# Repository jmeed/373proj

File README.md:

373proj
=======

The Smart Watch Project

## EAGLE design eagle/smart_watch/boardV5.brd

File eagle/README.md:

Before you open the file in eagle make sure to go to library->use and add all the files in the lbr directory

Major Links for Documentation

ARM M-0
* LCP 1114 48 pin : http://www.nxp.com/documents/data_sheet/LPC111X.pdf

Power System:
* MAX17043G+U (Fuel Gage): http://dlnmh9ip6v2uc.cloudfront.net/datasheets/Prototyping/MAX17043-MAX17044.pdf 
 * I2C
* MCP73831T (Battery Charger): http://www.sparkfun.com/datasheets/Prototyping/Batteries/MCP73831T.pdf
* TPS61200 (Boost Converter): http://www.sparkfun.com/datasheets/Prototyping/tps61200.pdf
* MIC5205 (LDO) : http://www.micrel.com/_PDF/mic5205.pdf

Screen: 
* uOLED-G2 : http://www.4dsystems.com.au/downloads/microOLED/uOLED-128-G2/Docs/uOLED-128-G2-Datasheet-REV1.pdf
			 Serial Communication documentation: http://www.4dsystems.com.au/downloads/Software/4D-Workshop4-IDE/Docs/Serial/GOLDELOX-SPE-COMMAND-SET-REV1.3.pdf
  * UART

Bluetooth:
* SPI/UART
  
Perf:
* ADXL345 (Accelerometer): http://www.sparkfun.com/datasheets/Sensors/Accelerometer/ADXL345.pdf
  * SPI/I2C
* Vibrator (2 pins) 
  * 1 pin gpio. Other pin gnd
* Joystick : http://www.sparkfun.com/datasheets/Components/Buttons/SF303GJ26-3.pdf
  *  NOTE: I am not sure how to get this on the board as it is big and the board will be covered on both sides.
  *  5 pins GPIO. 1 pin power

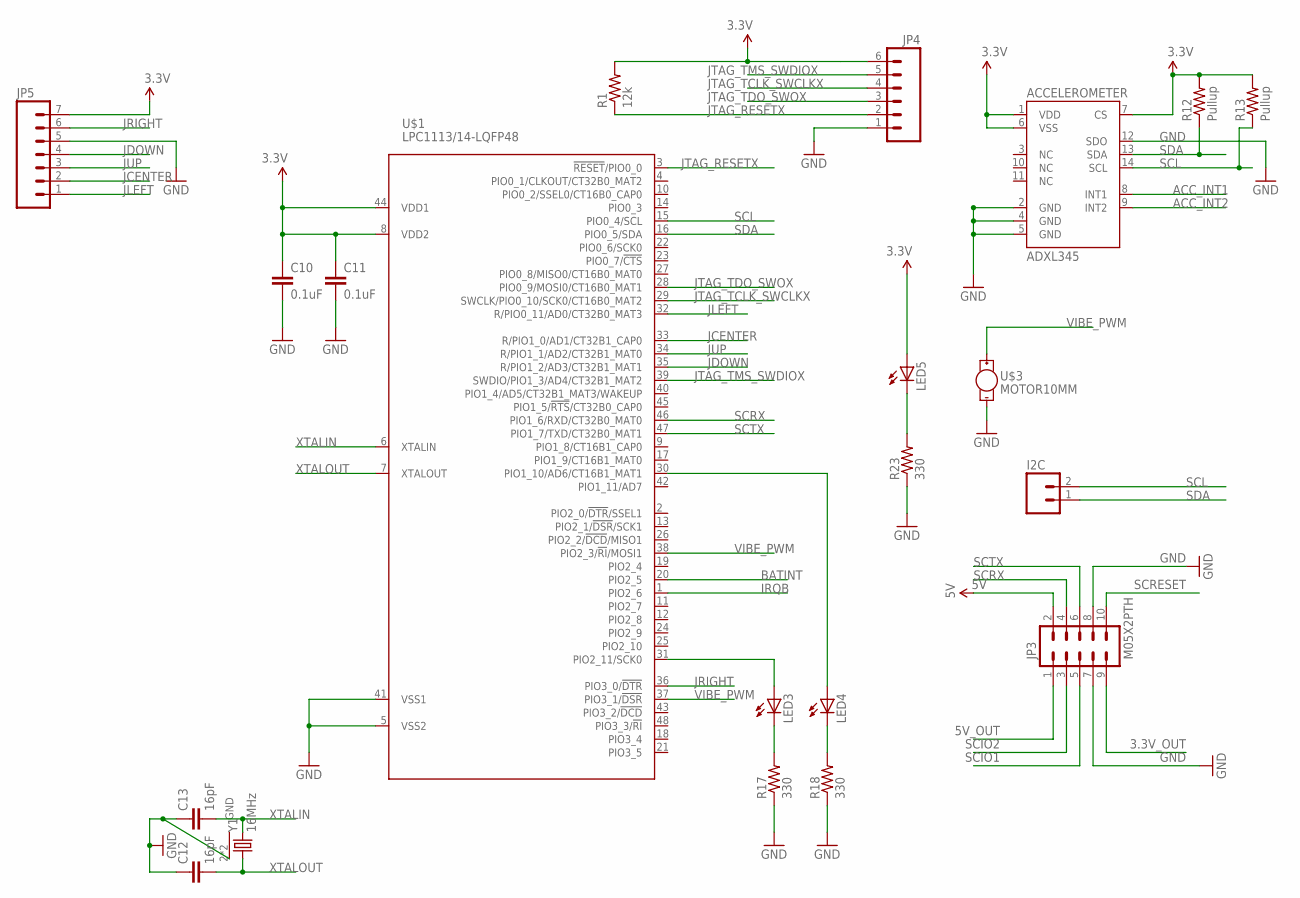
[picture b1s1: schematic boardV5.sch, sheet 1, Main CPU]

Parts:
ACCELEROMETER: ADXL345; LGA14
C10, C11: 0.1uF; 0603-CAP
C12, C13: 16pF; 0603-CAP
I2C: M02POLAR; MOLEX-1X2
JP3: M05X2PTH; AVR_ICSP
JP4: M06POLAR; MOLEX-1X6
JP5: M07; 1X07
LED3, LED4, LED5: LED0603; LED-0603
R1: 12k; 0603-RES
R12, R13: Pullup; 0603-RES
R17, R18, R23: 330; 0603-RES
U$1: LPC1113/14-LQFP48; LQFP48
U$3: MOTOR10MM; VIBE-MOTOR-10MM
Y1: 16MHz; CRYSTAL-SMD-5X3

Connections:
3.3V: ACCELEROMETER.1 (VDD), ACCELEROMETER.6 (VSS), ACCELEROMETER.7 (CS), C10.1, C11.1, JP4.6, JP5.7, LED5.A, R1.2, R12.2, R13.2, U$1.8 (VDD2), U$1.44 (VDD1); also elsewhere on the board
3.3V_OUT: JP3.9
5V: JP3.2; also elsewhere on the board
5V_OUT: JP3.1
ACC_INT1: ACCELEROMETER.8 (INT1)
ACC_INT2: ACCELEROMETER.9 (INT2)
BATINT: U$1.20 (PIO2_5); also elsewhere on the board
GND: ACCELEROMETER.2 (GND), ACCELEROMETER.4 (GND), ACCELEROMETER.5 (GND), ACCELEROMETER.12 (SDO), C10.2, C11.2, C12.1, C13.1, JP3.7, JP3.8, JP4.1, JP5.5, R17.1, R18.1, R23.1, U$1.5 (VSS2), U$1.41 (VSS1), U$3.-, Y1.2 (GND), Y1.4 (GND); also elsewhere on the board
IRQB: U$1.1 (PIO2_6); also elsewhere on the board
JCENTER: JP5.2, U$1.33 (R/PIO1_0/AD1/CT32B1_CAP0)
JDOWN: JP5.4, U$1.35 (R/PIO1_2/AD3/CT32B1_MAT1)
JLEFT: JP5.1, U$1.32 (R/PIO0_11/AD0/CT32B0_MAT3)
JRIGHT: JP5.6, U$1.36 (PIO3_0/!DTR!)
JTAG_RESETX: JP4.2, R1.1, U$1.3 (!RESET!/PIO0_0)
JTAG_TCLK_SWCLKX: JP4.4, U$1.29 (SWCLK/PIO0_10/SCK0/CT16B0_MAT2)
JTAG_TDO_SWOX: JP4.3, U$1.28 (PIO0_9/MOSI0/CT16B0_MAT1)
JTAG_TMS_SWDIOX: JP4.5, U$1.39 (SWDIO/PIO1_3/AD4/CT32B1_MAT2)
JUP: JP5.3, U$1.34 (R/PIO1_1/AD2/CT32B1_MAT0)
unnamed: LED3.A, U$1.31 (PIO2_11/SCK0)
unnamed: LED4.A, U$1.30 (PIO1_10/AD6/CT16B1_MAT1)
unnamed: LED3.C, R17.2
unnamed: LED4.C, R18.2
unnamed: LED5.C, R23.2
SCIO1: JP3.5
SCIO2: JP3.3
SCL: ACCELEROMETER.14 (SCL), I2C.2, R13.1, U$1.15 (PIO0_4/SCL); also elsewhere on the board
SCRESET: JP3.10
SCRX: JP3.4, U$1.46 (PIO1_6/RXD/CT32B0_MAT0)
SCTX: JP3.6, U$1.47 (PIO1_7/TXD/CT32B0_MAT1)
SDA: ACCELEROMETER.13 (SDA), I2C.1, R12.1, U$1.16 (PIO0_5/SDA); also elsewhere on the board
VIBE_PWM: U$1.37 (PIO3_1/!DSR!), U$1.38 (PIO2_3/!RI!/MOSI1), U$3.+
XTALIN: C13.2, U$1.6 (XTALIN), Y1.3 (2)
XTALOUT: C12.2, U$1.7 (XTALOUT), Y1.1

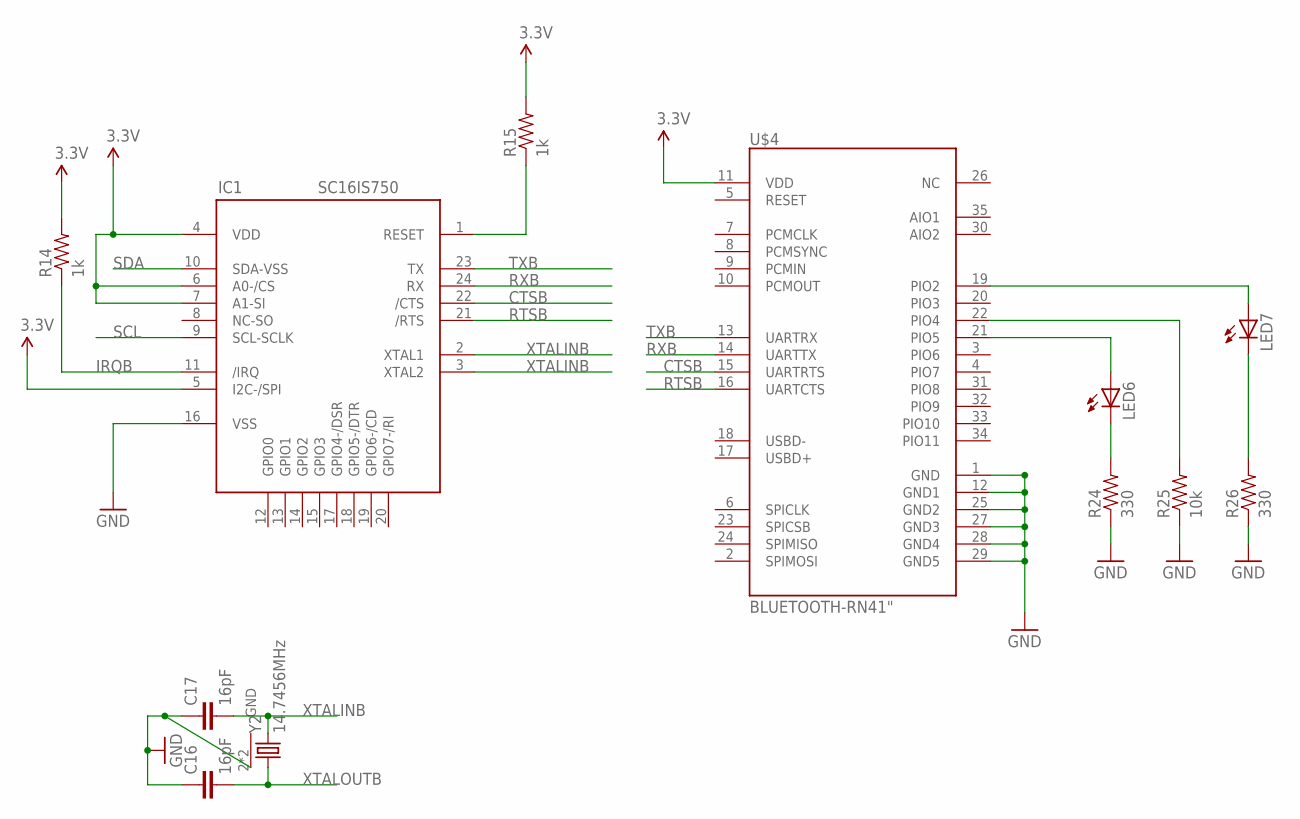
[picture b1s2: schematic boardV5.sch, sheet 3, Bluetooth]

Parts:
C16, C17: 16pF; 0603-CAP
IC1: SC16IS750; QFN-24
LED6, LED7: LED0603; LED-0603
R14, R15: 1k; 0603-RES
R24, R26: 330; 0603-RES
R25: 10k; 0603-RES
U$4: BLUETOOTH-RN41"; RN41
Y2: 14.7456MHz; CRYSTAL-SMD-5X3

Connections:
3.3V: IC1.4 (VDD), IC1.5 (I2C-/SPI), IC1.6 (A0-/CS), IC1.7 (A1-SI), R14.2, R15.2, U$4.11 (VDD); also elsewhere on the board
CTSB: IC1.22 (/CTS), U$4.15 (UARTRTS)
GND: C16.1, C17.1, IC1.16 (VSS), R24.1, R25.1, R26.1, U$4.1 (GND), U$4.12 (GND1), U$4.25 (GND2), U$4.27 (GND3), U$4.28 (GND4), U$4.29 (GND5), Y2.2 (GND), Y2.4 (GND); also elsewhere on the board
IRQB: IC1.11 (/IRQ), R14.1; also elsewhere on the board
unnamed: IC1.1 (RESET), R15.1
unnamed: LED7.A, U$4.19 (PIO2)
unnamed: R25.2, U$4.22 (PIO4)
unnamed: LED6.A, U$4.21 (PIO5)
unnamed: LED6.C, R24.2
unnamed: LED7.C, R26.2
RTSB: IC1.21 (/RTS), U$4.16 (UARTCTS)
RXB: IC1.24 (RX), U$4.14 (UARTTX)
SCL: IC1.9 (SCL-SCLK); also elsewhere on the board
SDA: IC1.10 (SDA-VSS); also elsewhere on the board
TXB: IC1.23 (TX), U$4.13 (UARTRX)
XTALINB: C17.2, IC1.2 (XTAL1), Y2.3 (2)
XTALOUTB: C16.2, IC1.3 (XTAL2), Y2.1

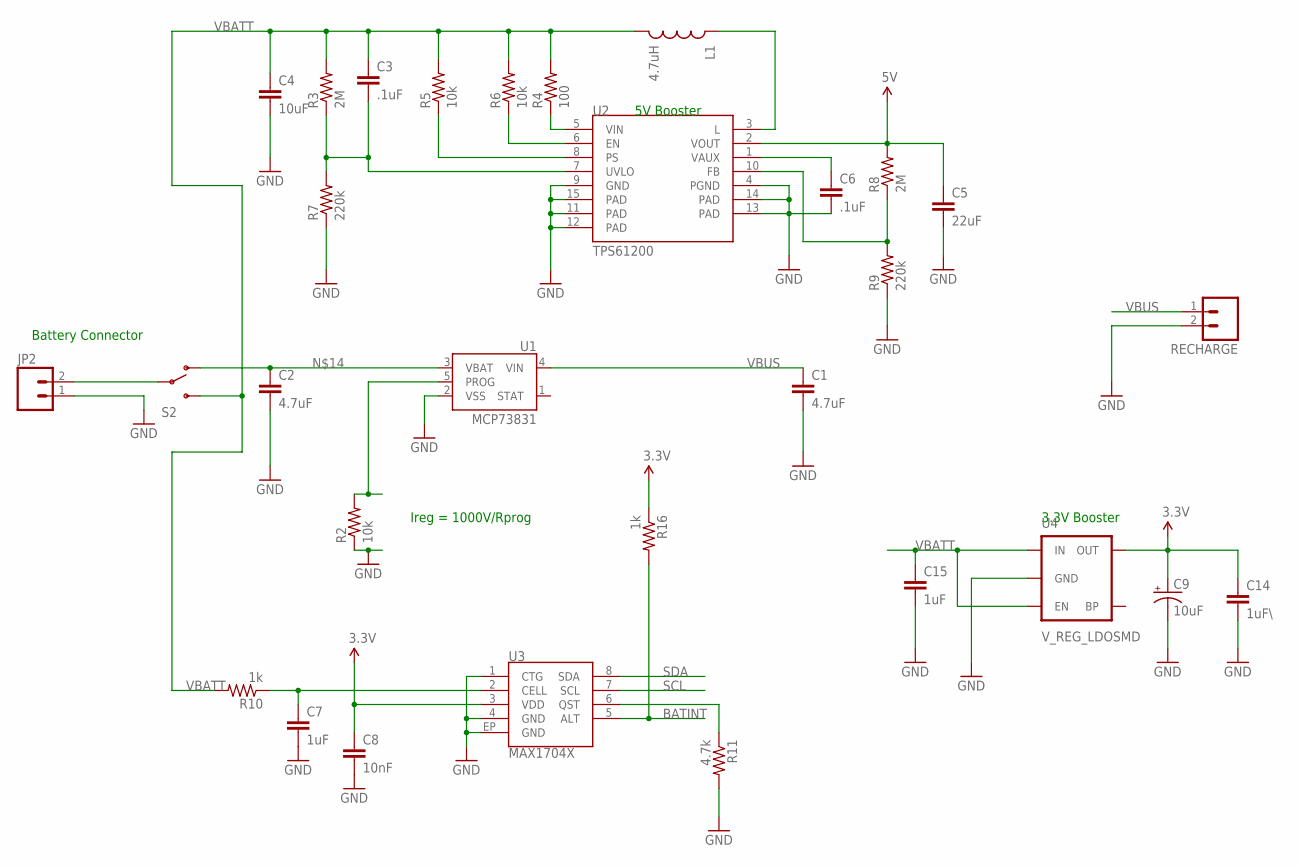
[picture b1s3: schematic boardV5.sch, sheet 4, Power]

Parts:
C1, C2: 4.7uF; 0603-CAP
C3, C6: .1uF; 0603-CAP
C4: 10uF; 0603-CAP
C5: 22uF; 0603-CAP
C7, C15: 1uF; 0603-CAP
C8: 10nF; 0603-CAP
C9: 10uF; EIA3216
C14: 1uF\; 0603-CAP
JP2: M02PTH; 1X02
L1: 4.7uH; CDRH2D09
R2, R5, R6: 10k; 0603-RES
R3, R8: 2M; 0603-RES
R4: 100; 0603-RES
R7, R9: 220k; 0603-RES
R10, R16: 1k; 0603-RES
R11: 4.7k; 0603-RES
RECHARGE: M02POLAR; MOLEX-1X2
S2: SWITCH-SPDT-SMD-A; SWITCH-SPST-SMD-A
U1: MCP73831; SOT23-5
U2: TPS61200; QFN-10_PAD
U3: MAX1704X; TDFN-8
U4: V_REG_LDOSMD; SOT23-5

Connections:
3.3V: C8.1, C9.A (+), C14.1, R16.1, U3.3 (VDD), U4.5 (OUT); also elsewhere on the board
5V: C5.1, R8.2, U2.2 (VOUT); also elsewhere on the board
BATINT: R16.2, U3.5 (ALT); also elsewhere on the board
GND: C1.2, C2.2, C4.2, C5.2, C6.2, C7.2, C8.2, C9.C (-), C14.2, C15.2, JP2.1, R2.1, R7.1, R9.1, R11.2, RECHARGE.2, U1.2 (VSS), U2.4 (PGND), U2.9 (GND), U2.11 (PAD), U2.12 (PAD), U2.13 (PAD), U2.14 (PAD), U2.15 (PAD), U3.1 (CTG), U3.4 (GND), U3.EP (GND), U4.2 (GND); also elsewhere on the board
unnamed: R2.2, U1.5 (PROG)
unnamed: C3.2, R3.1, R7.2, U2.7 (UVLO)
unnamed: C6.1, U2.1 (VAUX)
unnamed: R6.1, U2.6 (EN)
unnamed: R5.1, U2.8 (PS)
unnamed: L1.P$1 (1), U2.3 (L)
unnamed: R8.1, R9.2, U2.10 (FB)
unnamed: C7.1, R10.1, U3.2 (CELL)
unnamed: R11.1, U3.6 (QST)
unnamed: C2.1, S2.1 (O), U1.3 (VBAT)
unnamed: JP2.2, S2.2
SCL: U3.7 (SCL); also elsewhere on the board
SDA: U3.8 (SDA); also elsewhere on the board
VBATT: C3.1, C4.1, C15.1, L1.P$2 (2), R3.2, R4.2, R5.2, R6.2, R10.2, S2.3 (S), U4.1 (IN), U4.3 (EN)
VBUS: C1.1, RECHARGE.1, U1.4 (VIN)
VIN: R4.1, U2.5 (VIN)

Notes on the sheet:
Ireg = 1000V/Rprog
Battery Connector
5V Booster
3.3V Booster

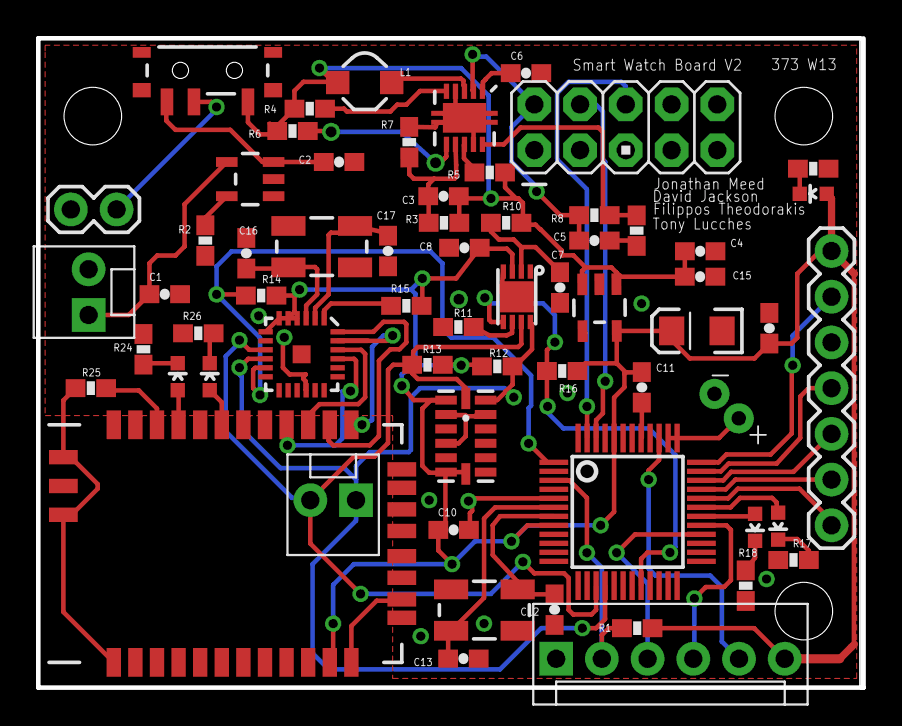
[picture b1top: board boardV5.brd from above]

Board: 2 copper layers, 45.8 x 36.1 mm, 63 parts (0 on the bottom side), 52 nets.

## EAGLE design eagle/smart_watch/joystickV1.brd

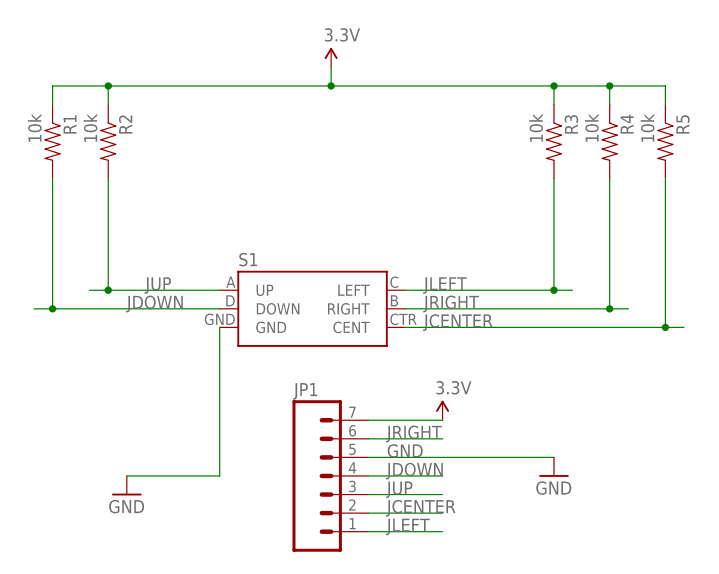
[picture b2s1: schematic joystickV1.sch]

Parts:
JP1: M07; 1X07
R1, R2, R3, R4, R5: 10k; 0603-RES
S1: JOYSTICK_MINI

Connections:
3.3V: JP1.7, R1.1, R2.1, R3.1, R4.1, R5.1
GND: JP1.5, S1.GND
JCENTER: JP1.2, R5.2, S1.CTR (CENT)
JDOWN: JP1.4, R1.2, S1.D (DOWN)
JLEFT: JP1.1, R3.2, S1.C (LEFT)
JRIGHT: JP1.6, R4.2, S1.B (RIGHT)
JUP: JP1.3, R2.2, S1.A (UP)

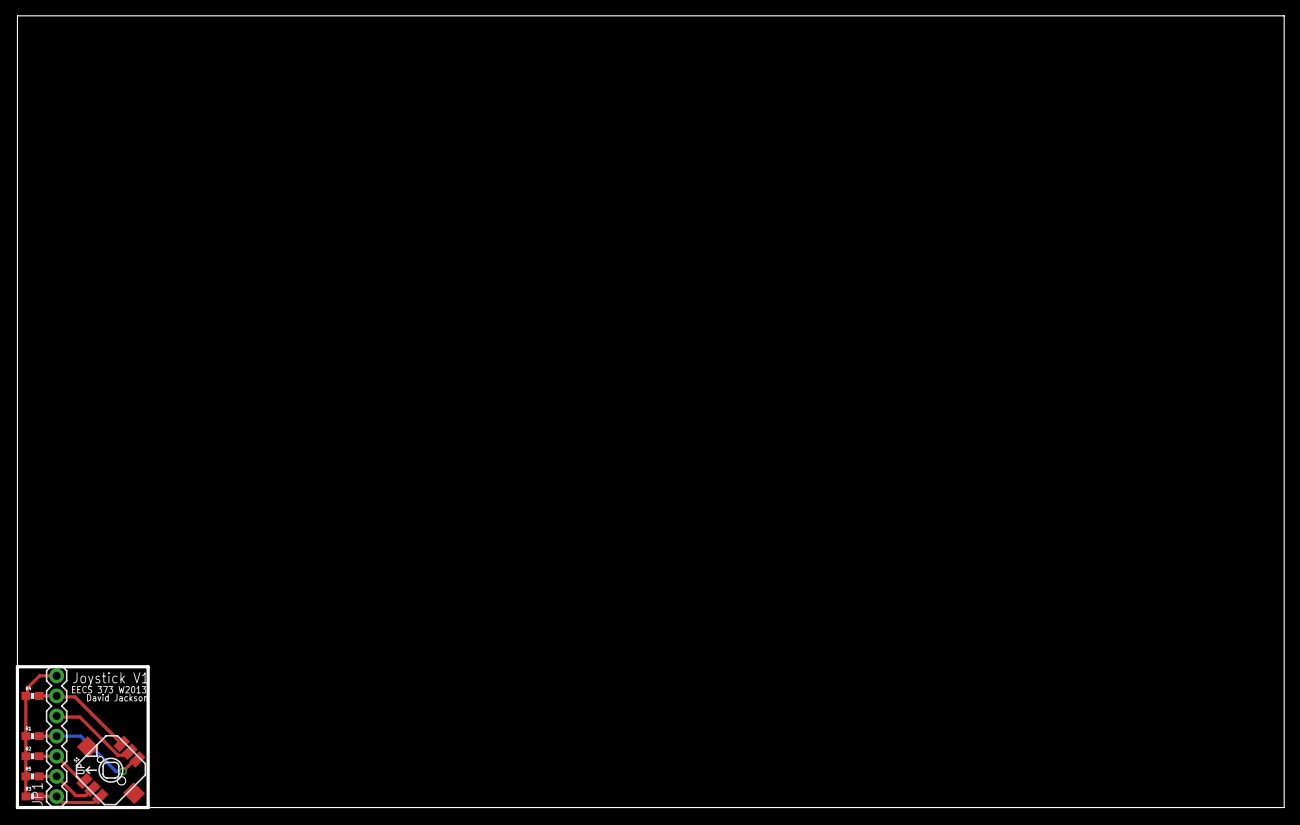
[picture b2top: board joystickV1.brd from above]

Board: 2 copper layers, 160.0 x 100.0 mm, 7 parts (0 on the bottom side), 7 nets.

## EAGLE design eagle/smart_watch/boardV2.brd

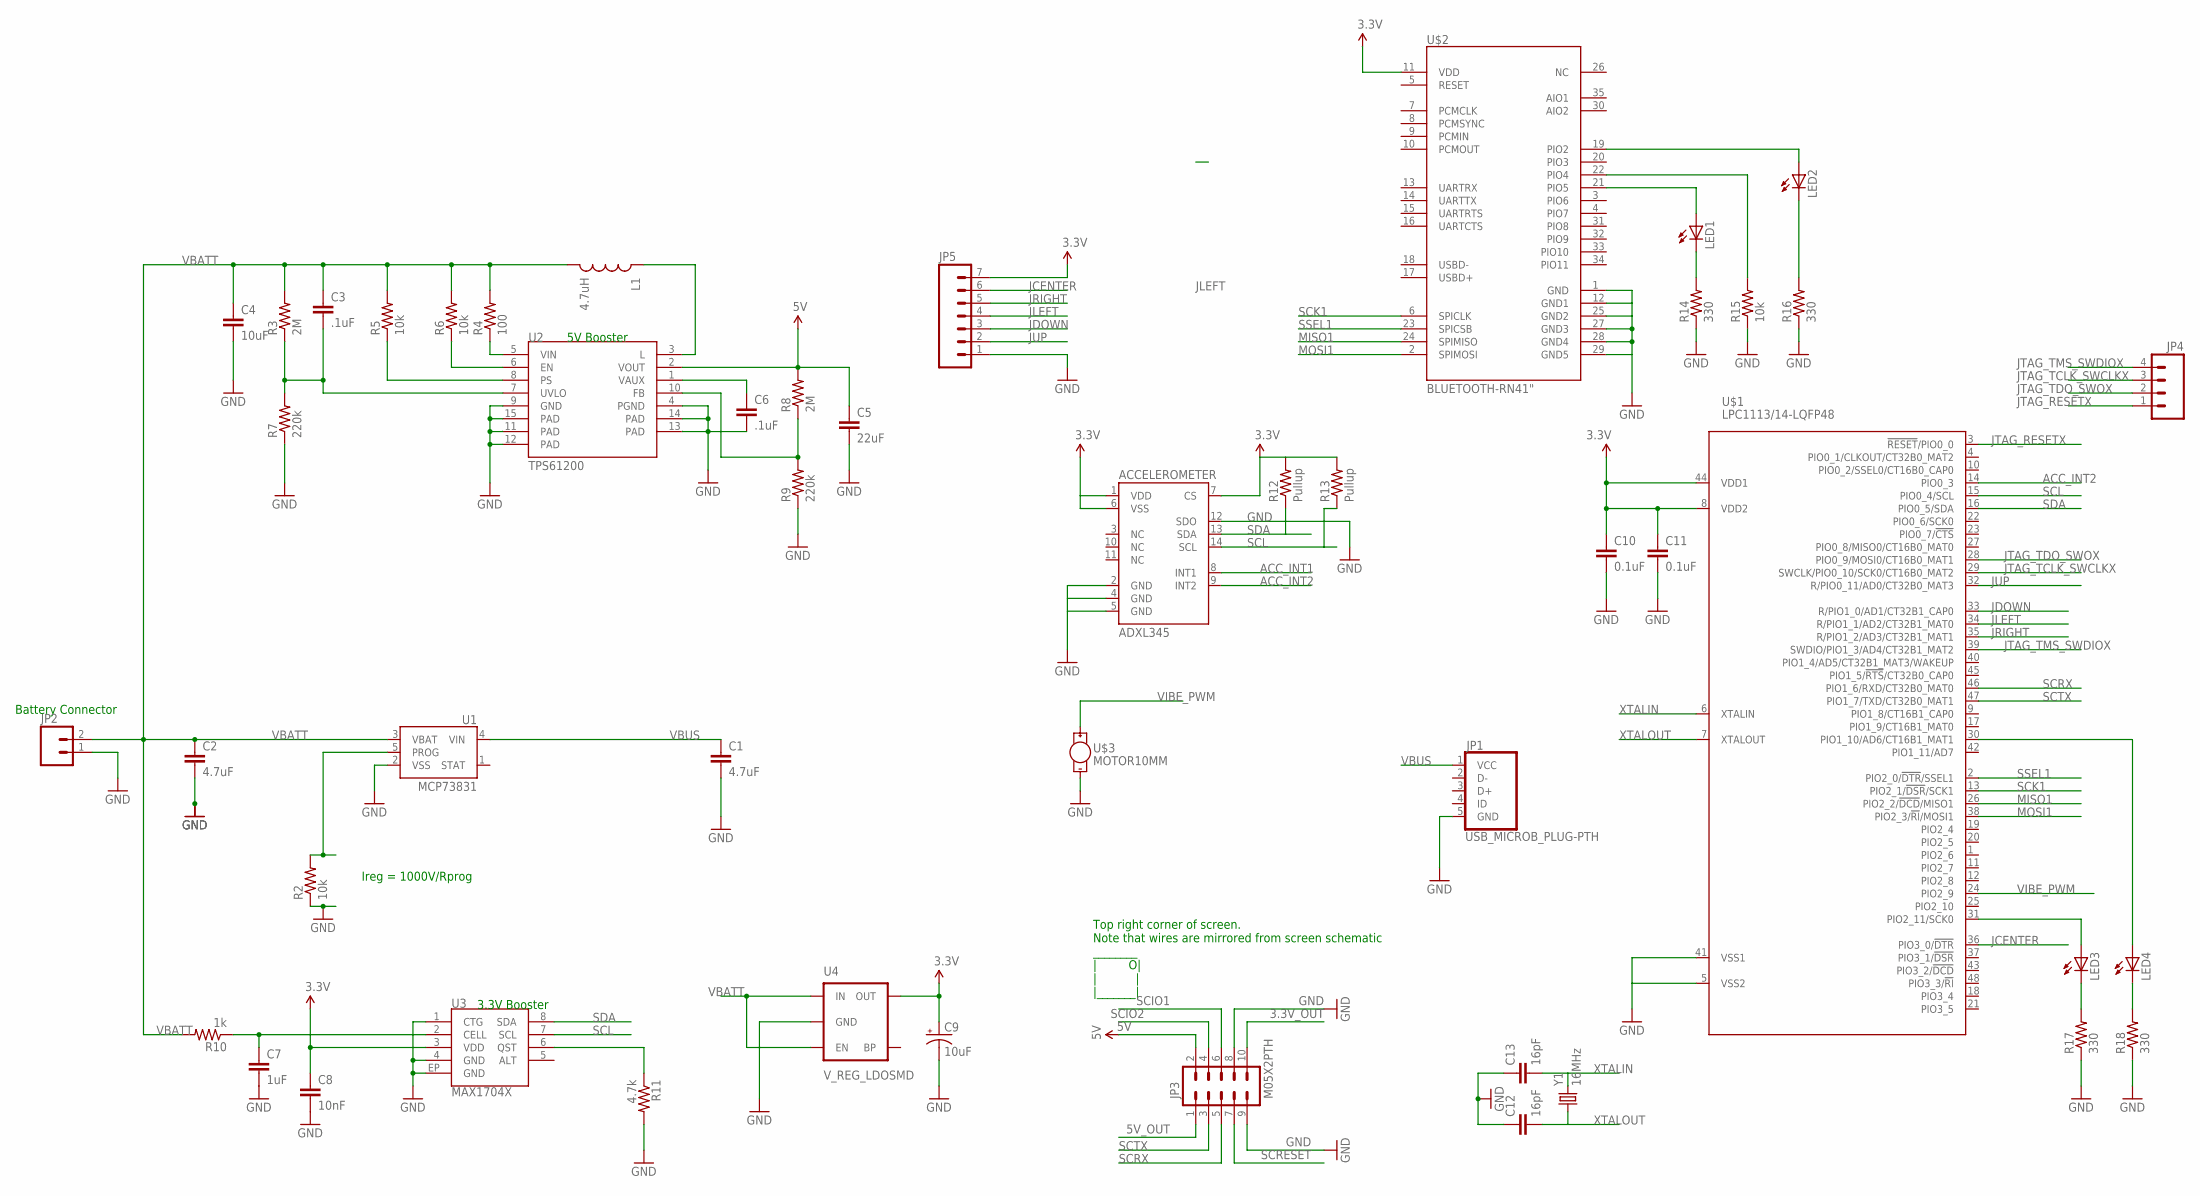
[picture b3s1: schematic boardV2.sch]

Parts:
ACCELEROMETER: ADXL345; LGA14
C1, C2: 4.7uF; 0402-CAP
C3, C6: .1uF; 0402-CAP
C4: 10uF; 0402-CAP
C5: 22uF; 0402-CAP
C7: 1uF; 0402-CAP
C8: 10nF; 0402-CAP
C9: 10uF; EIA3216
C10, C11: 0.1uF; 0402-CAP
C12, C13: 16pF; 0402-CAP
JP1: USB_MICROB_PLUG-PTH; MICRO-B-RA-TH
JP2: M02-JST-2-PTH-NO_SILK; JST-2-PTH-NS
JP3: M05X2PTH; AVR_ICSP
JP4: M04POLAR; MOLEX-1X4
JP5: M07; 1X07
L1: 4.7uH; C0402
LED1, LED2, LED3, LED4: LED0603; LED-0603
R2, R5, R6, R15: 10k; 0402-RES
R3, R8: 2M; 0402-RES
R4: 100; 0402-RES
R7, R9: 220k; 0402-RES
R10: 1k; 0402-RES
R11: 4.7k; 0402-RES
R12, R13: Pullup; 0402-RES
R14, R16, R17, R18: 330; 0402-RES
U1: MCP73831; SOT23-5
U2: TPS61200; QFN-10_PAD
U3: MAX1704X; TDFN-8
U4: V_REG_LDOSMD; SOT23-5
U$1: LPC1113/14-LQFP48; LQFP48
U$2: BLUETOOTH-RN41"; RN41
U$3: MOTOR10MM; VIBE-MOTOR-10MM
Y1: 16MHz; CRYSTAL-SMD-5X3

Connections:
3.3V: ACCELEROMETER.1 (VDD), ACCELEROMETER.6 (VSS), ACCELEROMETER.7 (CS), C8.1, C9.A (+), C10.1, C11.1, JP5.7, R12.2, R13.2, U3.3 (VDD), U4.5 (OUT), U$1.8 (VDD2), U$1.44 (VDD1), U$2.11 (VDD)
3.3V_OUT: JP3.10
5V: C5.1, JP3.2, R8.2, U2.2 (VOUT)
5V_OUT: JP3.1
ACC_INT1: ACCELEROMETER.8 (INT1)
ACC_INT2: ACCELEROMETER.9 (INT2), U$1.14 (PIO0_3)
GND: ACCELEROMETER.2 (GND), ACCELEROMETER.4 (GND), ACCELEROMETER.5 (GND), ACCELEROMETER.12 (SDO), C1.2, C2.2, C4.2, C5.2, C6.2, C7.2, C8.2, C9.C (-), C10.2, C11.2, C12.1, C13.1, JP1.5 (GND), JP2.1, JP3.8, JP3.9, JP5.1, R2.1, R7.1, R9.1, R11.2, R14.1, R15.1, R16.1, R17.1, R18.1, U1.2 (VSS), U2.4 (PGND), U2.9 (GND), U2.11 (PAD), U2.12 (PAD), U2.13 (PAD), U2.14 (PAD), U2.15 (PAD), U3.1 (CTG), U3.4 (GND), U3.EP (GND), U4.2 (GND), U$1.5 (VSS2), U$1.41 (VSS1), U$2.1 (GND), U$2.12 (GND1), U$2.25 (GND2), U$2.27 (GND3), U$2.28 (GND4), U$2.29 (GND5), U$3.-
JCENTER: JP5.6, U$1.36 (PIO3_0/!DTR!)
JDOWN: JP5.3, U$1.33 (R/PIO1_0/AD1/CT32B1_CAP0)
JLEFT: JP5.4, U$1.34 (R/PIO1_1/AD2/CT32B1_MAT0)
JRIGHT: JP5.5, U$1.35 (R/PIO1_2/AD3/CT32B1_MAT1)
JTAG_RESETX: JP4.1, U$1.3 (!RESET!/PIO0_0)
JTAG_TCLK_SWCLKX: JP4.3, U$1.29 (SWCLK/PIO0_10/SCK0/CT16B0_MAT2)
JTAG_TDO_SWOX: JP4.2, U$1.28 (PIO0_9/MOSI0/CT16B0_MAT1)
JTAG_TMS_SWDIOX: JP4.4, U$1.39 (SWDIO/PIO1_3/AD4/CT32B1_MAT2)
JUP: JP5.2, U$1.32 (R/PIO0_11/AD0/CT32B0_MAT3)
MISO1: U$1.26 (PIO2_2/!DCD!/MISO1), U$2.24 (SPIMISO)
MOSI1: U$1.38 (PIO2_3/!RI!/MOSI1), U$2.2 (SPIMOSI)
unnamed: LED2.A, U$2.19 (PIO2)
unnamed: R2.2, U1.5 (PROG)
unnamed: C3.2, R3.1, R7.2, U2.7 (UVLO)
unnamed: C6.1, U2.1 (VAUX)
unnamed: R6.1, U2.6 (EN)
unnamed: R5.1, U2.8 (PS)
unnamed: L1.1, U2.3 (L)
unnamed: R8.1, R9.2, U2.10 (FB)
unnamed: C7.1, R10.1, U3.2 (CELL)
unnamed: R11.1, U3.6 (QST)
unnamed: R15.2, U$2.22 (PIO4)
unnamed: LED1.A, U$2.21 (PIO5)
unnamed: LED1.C, R14.2
unnamed: LED2.C, R16.2
unnamed: LED3.A, U$1.31 (PIO2_11/SCK0)
unnamed: LED4.A, U$1.30 (PIO1_10/AD6/CT16B1_MAT1)
unnamed: LED3.C, R17.2
unnamed: LED4.C, R18.2
SCIO1: JP3.6
SCIO2: JP3.4
SCK1: U$1.13 (PIO2_1/!DSR!/SCK1), U$2.6 (SPICLK)
SCL: ACCELEROMETER.14 (SCL), R13.1, U3.7 (SCL), U$1.15 (PIO0_4/SCL)
SCRESET: JP3.7
SCRX: JP3.5, U$1.46 (PIO1_6/RXD/CT32B0_MAT0)
SCTX: JP3.3, U$1.47 (PIO1_7/TXD/CT32B0_MAT1)
SDA: ACCELEROMETER.13 (SDA), R12.1, U3.8 (SDA), U$1.16 (PIO0_5/SDA)
SSEL1: U$1.2 (PIO2_0/!DTR!/SSEL1), U$2.23 (SPICSB)
VBATT: C2.1, C3.1, C4.1, JP2.2, L1.2, R3.2, R4.2, R5.2, R6.2, R10.2, U1.3 (VBAT), U4.1 (IN), U4.3 (EN)
VBUS: C1.1, JP1.1 (VCC), U1.4 (VIN)
VIBE_PWM: U$1.24 (PIO2_9), U$3.+
VIN: R4.1, U2.5 (VIN)
XTALIN: C13.2, U$1.6 (XTALIN), Y1.3 (2)
XTALOUT: C12.2, U$1.7 (XTALOUT), Y1.1

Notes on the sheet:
Ireg = 1000V/Rprog
Battery Connector
5V Booster
3.3V Booster
Top right corner of screen. Note that wires are mirrored from screen schematic ________ | O| | | |_______|

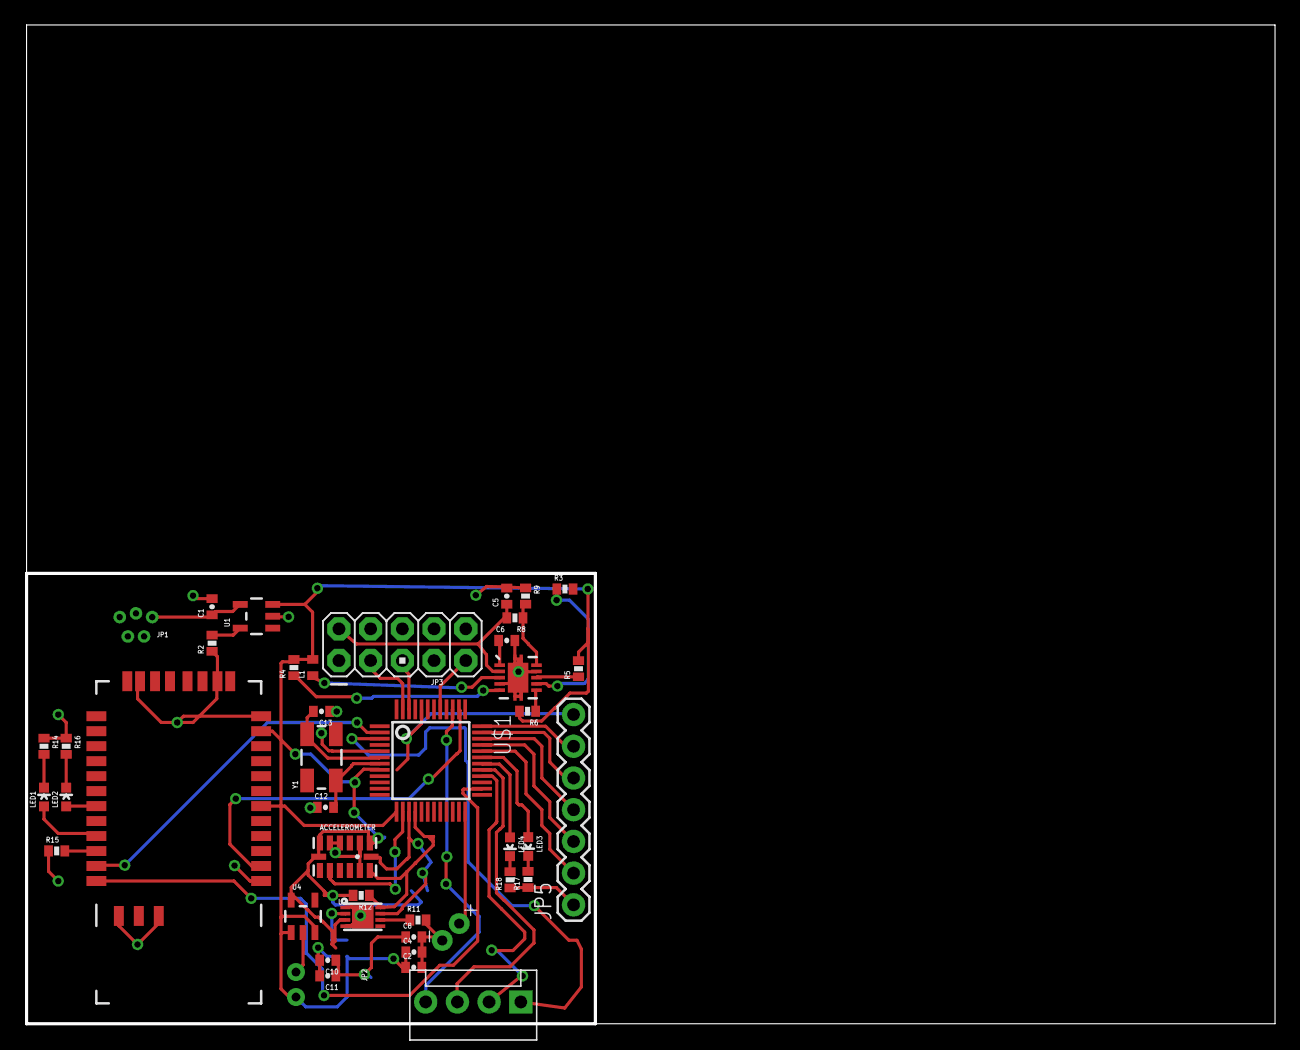
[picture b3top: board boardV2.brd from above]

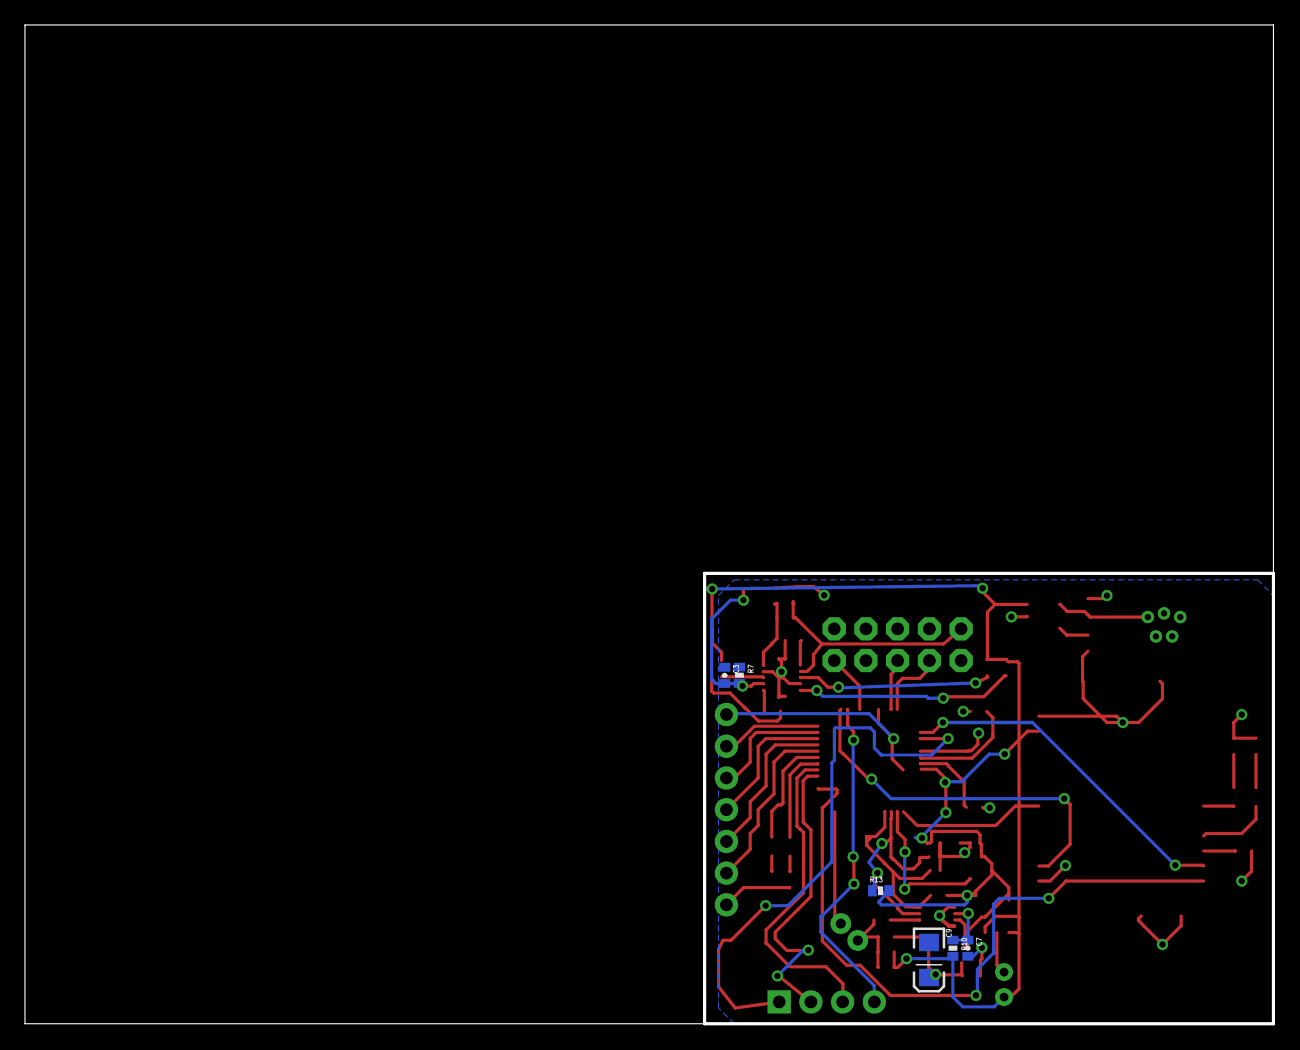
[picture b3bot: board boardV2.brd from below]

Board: 2 copper layers, 100.0 x 80.0 mm, 49 parts (6 on the bottom side), 45 nets.

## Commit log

2013-03-06 Added library files for eagle
2013-03-06 Added basic power circuit
2013-03-06 added readme for hardware :
2013-03-06 test
2013-03-06 added gitignore
2013-03-06 modded gitignore
2013-03-07 Added board
2013-03-07 wierd git stuff
2013-03-07 Finally fixed .gitignore
2013-03-07 Update README.md
    Added arm link
2013-03-08 V1 of Schema is donepending feedback
2013-03-08 added board schema image
2013-03-08 Started layout Fixed up joystick wiring
2013-03-09 Finished V1 of board layout
2013-03-09 Added picture of layout
2013-03-12 update before I start on V2
2013-03-12 Complete redesign of the board, this time with all the mounting holes in the right spot
2013-03-13 Started work on V3 after Sams Comments
2013-03-14 Added Joystick schematic and board
2013-03-15 Finished off V3 board design. Added silk to boards
2013-03-17 updated .gitignore
2013-03-17 Board and schema going out for review
2013-03-17 Out for review
2013-03-19 Updated board based on Sam's recs
2013-03-21 Created Gerber Files. Ready to be sent for printing.
2013-03-21 Updated usb port and changed some res sizes
2013-03-24 Added NXP Test LED & Motor code
2013-03-24 Adjusted NXP test. Interrupts known unworking.
2013-03-25 Some updates with git
2013-03-25 Did a little of bit of tweeks on the wireing
2013-03-26 Fixed up git ignore for xpress;
2013-03-26 Started on V4
2013-03-26 Some more tweaks
2013-03-27 Did a bunch of routing, woo... woo!!! woo?
2013-03-27 fixed up gitignore
2013-03-27 version 4.0 all connected
2013-03-28 Fixed a small error
2013-03-29 Screen demo code - SHIT DOESN'T WORK GODDAMMIT
    fuck
2013-03-29 updating .gitignore to remove all metadata. Removing all metadata
2013-03-29 Revert "Screen demo code - SHIT DOESN'T WORK GODDAMMIT"
    This reverts commit aea52f6cee7c308a68cef1beb12688705ac6d465.
2013-03-29 Revert "Revert "Screen demo code - SHIT DOESN'T WORK GODDAMMIT""
    This reverts commit f042096c783f8e1c083d1db0828e8e3168f46685.
2013-03-30 Started the Android app
2013-03-31 Android app now seraches for available devices
2013-03-31 Can connect to the bluetooth and send a basic synnc message
2013-03-31 Added Bluetooth service files for connecting to a bluetooth device
2013-03-31 Added a copy of the led test to start working on the bluetooth on the NXP instead of the Smartfusion
2013-04-01 The bluesmirf and the nexus can now send the initial authentication message back and forth. Bluesmirf used interrupts through UART port. Things seem to work but still need to create the rest of the m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
2013-04-02 Added i2c example for the bluetooth to start testing
2013-04-02 Trying I2C but things are not working
2013-04-03 Accelerometer getting data works
2013-04-03 FUCK. The. Screen.
2013-04-05 Working on adding i2c to uart capabilities
2013-04-05 Made a few minor changes to board V4, added V5 with edits for printing. TODO: Wiring of board V5. See email for other additions
2013-04-05 Working on getting the bluetooth i2c to uart working. We seem to have the resiters set correctly
2013-04-05 Added read and write function for registers
2013-04-05 I WILL BREAK THIS STUPID I2C UART BOARDgit add .git add .
2013-04-05 Finally I am reading something from stupid UART I2C. Yeahhh
2013-04-05 Interrupts not working but able to get the data. Will give up for now
2013-04-06 Working field gague too
2013-04-07 Documentation sheets, switch interrupts on NXP
2013-04-07 Can now receive and send from bluetooth. Tested with android app authentication messagew
2013-04-07 Working bluetooth better code. Fuel gauge should work but haven't tested it yet
2013-04-08 Creating android_final_app. App parses through weather and headlines and splits strings into less than 255 in length. Also converts each char to hex value. Ready to connect this app with bluetooth.
2013-04-09 Git commit. Finished and printed board V5
2013-04-10 I2C intergration completed and all parts are working
2013-04-10 Cleaned up code of I2C
2013-04-10 turned on all interupts on extint
2013-04-10 Wrote a bunch of code for the screen. Needs testing.
2013-04-10 committing android app. gets weather, headlines and current time. sends all over bluetooth successfully.
2013-04-11 More screen functionality enabled. Yay. Get some.
    I want a beer.
2013-04-11 Tony did a bunch of things
2013-04-12 implemented and tested string parsing function. bluetooth recieve needs to be tested. code needs to be cleaned up.
2013-04-12 updated bluetooth application. tested and works. parses all strings. inserts newline and does not split up words. code is cleaned up.
2013-04-12 Cleaning up repo
2013-04-13 stuff
2013-04-13 More screen stuff
    alkhfd
2013-04-13 Added the files for the MWatch OS
2013-04-13 Adding weather
2013-04-13 Added skeleton code for the states
2013-04-13 Screen
2013-04-13 Added screen images
2013-04-13 Added uart initialization
2013-04-13 asdkh
2013-04-13 added and enabled joystick GPIO
2013-04-13 BUFSIZEUART
2013-04-13 resolved merge
2013-04-13 stability
2013-04-13 weather enum
2013-04-13 added joystick enum
2013-04-13 HERRO
2013-04-13 got joystick interupts working
2013-04-13 bad something
2013-04-13 ;Got rid of debug shit
2013-04-14 Added i2c and bletot code
2013-04-14 Finally removed debug
2013-04-14 Fixed gitignore
2013-04-14 Added uart properties
2013-04-14 might break things:
2013-04-14 android app updated with new bluetooth stuff
2013-04-14 Added bluetooth main message code
2013-04-14 uart.h and uart.c change
2013-04-14 Turned on timers and uart and got the screen working
2013-04-14 Added fuel gauge and accelerometer
2013-04-14 Tay Zonday - Chocolate Rain
2013-04-14 added getJoyDirection
2013-04-14 Fixed stuff with bluetooth code and added documentation
2013-04-14 Minor change in old bluetooth code
2013-04-14 asdf
2013-04-14 Smll changes in the weather screen
2013-04-14 Reorganized the files for easier access
2013-04-14 Deleted uneccesary files
2013-04-14 removed .laucnh files, hopefulyl that doesn't break things
2013-04-14 Bluetooth works with joystic and android. The weather ia able to be send back and forth
2013-04-15 Now bl_send is constant to avoid modifying it
2013-04-15 updated bluetooth android app. Bluetooth should work. Currently, a lot of needed code is commented out to enable testing without bluetooth
2013-04-15 updated android app to interface with bluetooth
2013-04-16 Working weather
2013-04-16 weather works
2013-04-16 Fixed issue?
2013-04-16 Working watch, weather and headline screen
2013-04-16 same as previous. weather and headlines and time.
2013-04-16 Davids time fix
2013-04-16 Decreased printf
2013-04-16 screen speed & removed some printfs
2013-04-16 Set Baud Rate increased
2013-04-16 The screen works much better now and more responsive
2013-04-16 Can flash the chip and it works
2013-04-16 Renamed without a stupid underscore. GRRRRR
2013-04-17 Bluetooth on the new board is WORKING WHOREEEE WHOREEE WHOREEEE WHOREEE
2013-04-17 Now the accelerometer working
2013-04-17 Timer interrupts are working with the screen
2013-04-17 Time is working with system ticks now. It seems that its working
2013-04-17 Adjusted for greenwish time
2013-04-17 Working twoards screen and bluetooth timeouts
2013-04-17 Both screen and bluetooth timeouts seem to work
2013-04-17 Things
2013-04-17 Re-adjusting greenwisch time
2013-04-18 Added vibrator code
2013-04-18 updated app
2013-04-18 Added new bluetooth opcodes
2013-04-18 Adjust text size function built
2013-04-18 Now itme seem to be correct
2013-04-18 app updated
2013-04-18 Sort of working.
2013-04-18 Started working on snake
2013-04-18 Can initialize
2013-04-18 Got the right acc data
2013-04-18 Last stuff for snake
2013-04-20 Code that run in the Design expo
2013-04-22 Cleaned up look of application. Renamed to M-Watch. Parsed through forecast. will now display headlines better.
2013-04-22 will end in ... if string needs to be cut
2013-04-22 Fixed android app where it is going to wait forever untill it is connected instead of just failing if the watch is not turned on
2013-04-22 Android app can now detect a disconnect so that it starts searching again
2013-04-22 Added music control capability
2013-04-22 Almost working music control however it shows the previous song
2013-04-22 added music screen things
2013-04-23 final bluetooth app
2013-04-23 Our project.jpg
2013-04-23 Added volume control capability. Fixed issue where next song did not broadcast in Android. Small fixes in next song and delay to display longer screen and smaller wait times in bluetooth

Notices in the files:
parts and their libraries:
SparkFun-Connectors: Licensing: CC v3.0 Share-Alike You are welcome to use this library for commercial purposes.
